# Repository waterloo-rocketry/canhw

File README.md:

## RocketCAN Hardware

This repository tracks the hardware development for the RocketCAN project. All schematics, board designs, and fabrication files are tracked in this repository. The corresponding software running on each board can be found in the `cansw_*` repositories. The CAN driver library used is tracked in the `canlib` repository.

All hardware files were developed in KiCAD.

### System Architecture

The RocketCAN project is an extension of the 2018 Flight Instrumentation project. The functions of the original Flight Instrumentation electronics are decoupled into several single-function modules connected by a Controller Area Network (CAN bus). The 2019 RocketCAN configuration consists of a radio board, an injector valve driver, a vent valve driver, a flight sensor suite, a system logger, and a GPS receiver. The modules freely share information over the CAN bus, allowing all modules to access resources such as the radio transceiver and sensor module. This minimizes the amount of component and functionality duplication, as well as power consumption (especially by the radio module). Power consumption is reduced further by allowing the radio board to control power to the rest of the system, forcing it into a low-power state while the rocket is idle. The resulting PCBs are also significantly smaller and easier to mount inside the rocket. Finally, RocketCAN’s configuration is easily extensible. A new subsystem simply needs to include a CAN communication module, after which it can communicate with all other boards on the bus. Potential extensions such as a flight computer, a state estimation module, or an air braking system would be able to use existing sensor data without implementing their own independent sensor suite.

At present, the radio board integrates with Waterloo Rocketry's Remote Launch Control System (RLCS), from which it receives instructions. It is also capable of broadcasting sensor data to RLCS.  The radio board communicates with the tower-side box of RLCS, which relays the data to the client-side box at mission control.

The CAN protocol was chosen for its high data rate, priority-based arbitration, and abundance of inexpensive hardware. The bus can safely be used by many boards at once without the risk of a low-priority message (eg. sensor data) preempting a high-priority message (eg. valve command). Microcontrollers with CAN modules, stand-alone CAN modules, and CAN transceivers are all widely available, making it cheap and simple to add CAN functionality to a subsystem.

Further descriptions and instructions for using each individual board are available in the README in the relevant board's directory.

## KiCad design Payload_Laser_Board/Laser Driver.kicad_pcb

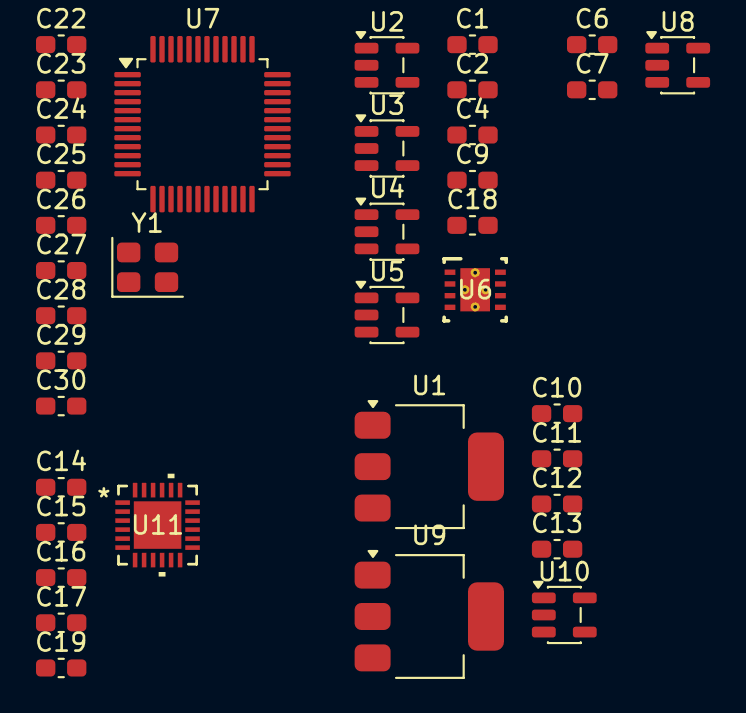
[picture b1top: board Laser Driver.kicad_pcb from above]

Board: 4 copper layers, 37 parts (0 on the bottom side), 25 nets, no tracks yet.

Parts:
C1: 0.47nF; C_0603_1608Metric_Pad1.08x0.95mm_HandSolder
C2: 2.2nF; C_0603_1608Metric_Pad1.08x0.95mm_HandSolder
C4, C9, C16, C17, C19, C25, C26: 0.1uF; C_0603_1608Metric_Pad1.08x0.95mm_HandSolder
C6: 35nF; C_0603_1608Metric_Pad1.08x0.95mm_HandSolder
C7: 160pF; C_0603_1608Metric_Pad1.08x0.95mm_HandSolder
C10, C11, C24, C27, C28, C29: 1uF; C_0603_1608Metric_Pad1.08x0.95mm_HandSolder
C12, C13, C22, C23: 2.2uF; C_0603_1608Metric_Pad1.08x0.95mm_HandSolder
C14, C15: 10uF; C_0603_1608Metric_Pad1.08x0.95mm_HandSolder
C18: 1nF; C_0603_1608Metric_Pad1.08x0.95mm_HandSolder
C30: 100nF; C_0603_1608Metric_Pad1.08x0.95mm_HandSolder
U1, U9: SPX2920M3-3.3_SOT223; SOT-223-3_TabPin2
U2, U3, U4, U5, U8: OPA364; SOT-23-5
U6: TPS73533QDRBRQ1; DRB0008B
U7: STM32H503CBTx; LQFP-48_7x7mm_P0.5mm
U10: INA160; SOT-23-5
U11: ADN8833ACPZ-R2; CP_24_7_ADI
Y1: ASE-8MHz; Oscillator_SMD_Abracon_ASE-4Pin_3.2x2.5mm

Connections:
+3.3VA: C4.1, C12.1, C24.2, U2.5 (V+), U3.5 (V+), U4.5 (V+), U5.5 (V+), U6.8 (IN), U7.9 (VDDA), U9.3 (VO)
+3.3VD: C13.1, C25.2, C26.2, C27.2, C28.2, C29.2, C30.2, U1.3 (VO), U7.1 (VBAT), U7.24 (VDD), U7.36 (VDD), U7.48 (VDD), U8.5 (V+), Y1.1 (EN), Y1.4 (Vdd)
+5V: C10.1, C11.1, C15.2, U1.1 (VI), U9.1 (VI), U10.3 (+), U11.15 (PVINS), U11.16 (PVINL)
/LASER_ENABLE_: C9.1, U6.5 (EN), U7.40 (PB4(NJTRST))
/MCU/CURRENT_SENSE: U7.18 (PB0), U10.1
/MCU/ITEC: U7.11 (PA1), U11.11 (TI_EC)
/MCU/OSC_IN: U7.5 (PH0), Y1.3 (OUT)
/MCU/VTEC: U7.12 (PA2), U11.9 (VTEC)
/MCU/VTEC_ENABLE: U7.13 (PA3), U11.2 (CONT)
/MCU/VTEC_ENB: U7.42 (PB6), U11.8 (EN_S/Y)
/SINE_SOURCE: C6.2, U7.15 (PA5)
GND: C4.2, C7.2, C9.2, C10.2, C11.2, C12.2, C13.2, C14.1, C15.1, C16.1, C17.1, C19.1, C22.1, C23.1, C24.1, C25.1, C26.1, C27.1, C28.1, C29.1, C30.1, U1.2 (GND), U2.2 (V-), U3.2 (V-), U4.2 (V-), U5.2 (V-), U6.4 (GND), U6.9 (PAD), U7.8 (VSSA), U7.23 (VSS), U7.35 (VSS), U7.47 (VSS), U8.2 (V-), U9.2 (GND), U10.2 (V-), U11.7 (AGND), U11.12 (PGNDS), U11.13 (PGNDS), U11.18 (PGNDL), U11.19 (PGNDL), U11.25 (EP), Y1.2 (GND)
unnamed: C22.2, U7.46 (VCAP)
unnamed: C23.2, U7.22 (VCAP)
unnamed: U2.1, U2.4 (-), U3.3 (+)
unnamed: U5.1, U5.4 (-)
unnamed: C2.1, C18.1, U6.1 (OUT)
unnamed: C17.2, U11.17 (LDR)
unnamed: C14.2, U11.10 (SFB)
unnamed: U3.4 (-), U4.1
unnamed: C18.2, U6.3 (FB)
unnamed: C7.1, U8.3 (+)
unnamed: U8.1, U8.4 (-)
unnamed: C16.2, U11.5 (VDD)
unnamed: C19.2, U11.6 (VREF)

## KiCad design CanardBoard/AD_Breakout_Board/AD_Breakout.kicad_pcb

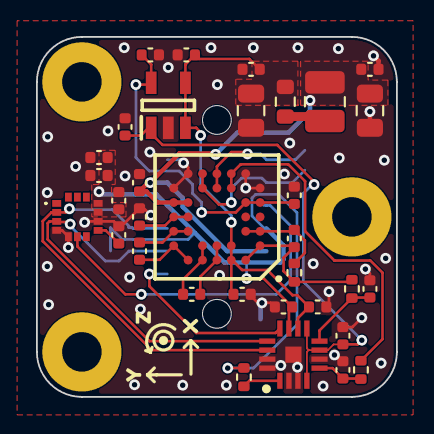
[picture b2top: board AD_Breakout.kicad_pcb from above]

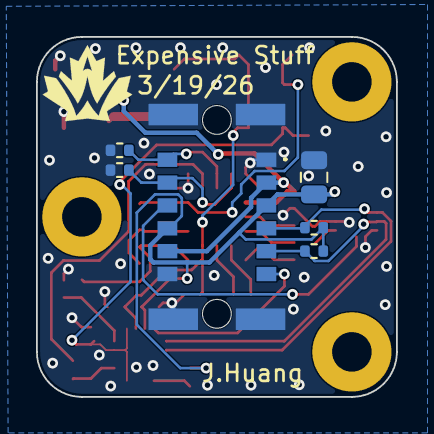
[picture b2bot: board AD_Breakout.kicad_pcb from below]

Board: 4 copper layers, 20.0 x 20.0 mm, 42 parts (6 on the bottom side), 25 nets.

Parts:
C1, C5, C7, C8, C11, C12, C13, C14, C15, C16, C19, C20, C22, C23, C24: 0.1uF; C_0402_1005Metric
C2, C3, C9: 22nF; C_0402_1005Metric
C4: 2.2nF; C_0402_1005Metric
C6: 6.8nF; C_0402_1005Metric
C10: 1uF; C_0402_1005Metric
C17, C18, C21: 10uF; C_0805_2012Metric
H1, H2, H3: M2; MountingHole_2.2mm_M2_Pad
J1: 1373827
L1: 2.2uH; L_1008_2520Metric
R1: 120k; R_0402_1005Metric
R2, R4: 3.3k; R_0402_1005Metric
R3, R5, R9: 10k; R_0402_1005Metric
R6, R7: 1k; R_0402_1005Metric
R8: 0.22R; R_0603_1608Metric
U1: ADXRS649BBGZ
U2: ADXL380
U3: ADS1219IRTER
U4: REF2041

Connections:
+2.048V_REF: C14.1, C24.1, U3.4 (AIN3), U3.7 (REFP), U3.9 (AIN0), U4.1 (VBIAS)
+3V3: C10.1, C11.1, C12.1, C16.1, C17.1, J1.A3, J1.B4, R6.1, R7.1, R9.1, U2.10 (VS), U2.11 (VDDIO), U3.11 (DVDD)
+4.096V_REF: C8.1, C23.1, U1.E1 (VRATIO_1), U1.E2 (VRATIO_2), U4.5 (VREF)
+5V: C1.1, C18.1, C19.1, J1.A2, J1.B5, L1.1, U1.E6 (VDD_1), U1.E7 (VDD_2)
+5VA: C5.1, C15.1, C20.1, C21.1, C22.1, R8.2, U1.A3 (AVCC_1), U1.B3 (AVCC_2), U3.10 (AVDD), U4.3 (EN), U4.4 (VIN)
/ADC/ADC_ALERT: J1.A6, U3.12 (~DRDY)
/ADC/ADI_SCL: J1.A4, R6.2, U2.2 (SCLK/SCL), U3.14 (SCL)
/ADC/ADI_SDA: J1.A5, R7.2, U2.3 (SDI/SDA), U3.13 (SDA)
/ADC/GYRO_OUT: C9.1, R4.2, U3.8 (AIN1)
/ADC/TEMP_OUT: C7.1, R2.2, U3.5 (AIN2)
/Accelerometer/ACCEL_INT: J1.B3, U2.6 (INT0)
/Gyroscope/TEMP: R2.1, U1.F3 (TEMP_1), U1.G3 (TEMP_2)
/ST1: J1.B2, R5.2, U1.F5 (ST1_1), U1.G5 (ST1_2)
/ST2: J1.B1, R3.2, U1.F4 (ST2_1), U1.G4 (ST2_2)
GND: C1.2, C4.2, C5.2, C7.2, C8.2, C9.2, C10.2, C11.2, C12.2, C13.2, C14.2, C15.2, C16.2, C17.2, C18.2, C19.2, C20.2, C21.2, C22.2, C23.2, C24.2, J1.A1, J1.B6, J1.MP1, J1.MP2, J1.MP3, J1.MP4, R3.1, R5.1, U1.F1 (AGND_1), U1.F7 (PGND_1), U1.G2 (AGND_2), U1.G6 (PGND_2), U2.4 (SDO/ASEL0), U2.5 (~CS/ASEL1), U2.9 (GND), U3.2 (DGND), U3.3 (AGND), U3.6 (REFN), U3.15 (A0), U3.16 (A1), U3.17 (EP), U4.2 (GND)
unnamed: L1.2, R8.1
unnamed: C2.1, U1.A5 (CP1_1), U1.B5 (CP1_2)
unnamed: C2.2, U1.A4 (CP2_1), U1.B4 (CP2_2)
unnamed: C3.1, U1.C6 (CP3_1), U1.C7 (CP3_2)
unnamed: C3.2, U1.A6 (CP4_1), U1.B7 (CP4_2)
unnamed: C4.1, U1.D6 (CP5_1), U1.D7 (CP5_2)
unnamed: C6.1, R1.2, R4.1, U1.A2 (RATEOUT_1), U1.B1 (RATEOUT_2)
unnamed: C6.2, R1.1, U1.C1 (SUMJ_1), U1.C2 (SUMJ_2)
unnamed: C13.1, U2.8 (V1P8)
unnamed: R9.2, U3.1 (~RESET)

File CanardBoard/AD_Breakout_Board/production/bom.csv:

Designator,Footprint,Quantity,Value,LCSC Part #
"C1, C11, C12, C13, C14, C15, C16, C19, C20, C22, C23, C24, C5, C7, C8",0402,15,0.1uF,
C10,0402,1,1uF,
"C17, C18, C21",0805,3,10uF,
"C2, C3, C9",0402,3,22nF,
C4,0402,1,2.2nF,
C6,0402,1,6.8nF,
J1,1373827,1,1373827,
L1,1008,1,2.2uH,LQM2HPN2R2MG0L
R1,0402,1,120k,
"R2, R4",0402,2,3.3k,
"R3, R5, R9",0402,3,10k,
"R6, R7",0402,2,1k,
R8,0603,1,0.22R,
U1,ADXRS649BBGZ,1,ADXRS649BBGZ,
U2,ADXL380,1,ADXL380,
U3,ADS1219IRTER,1,ADS1219IRTER,
U4,REF2041,1,REF2041,

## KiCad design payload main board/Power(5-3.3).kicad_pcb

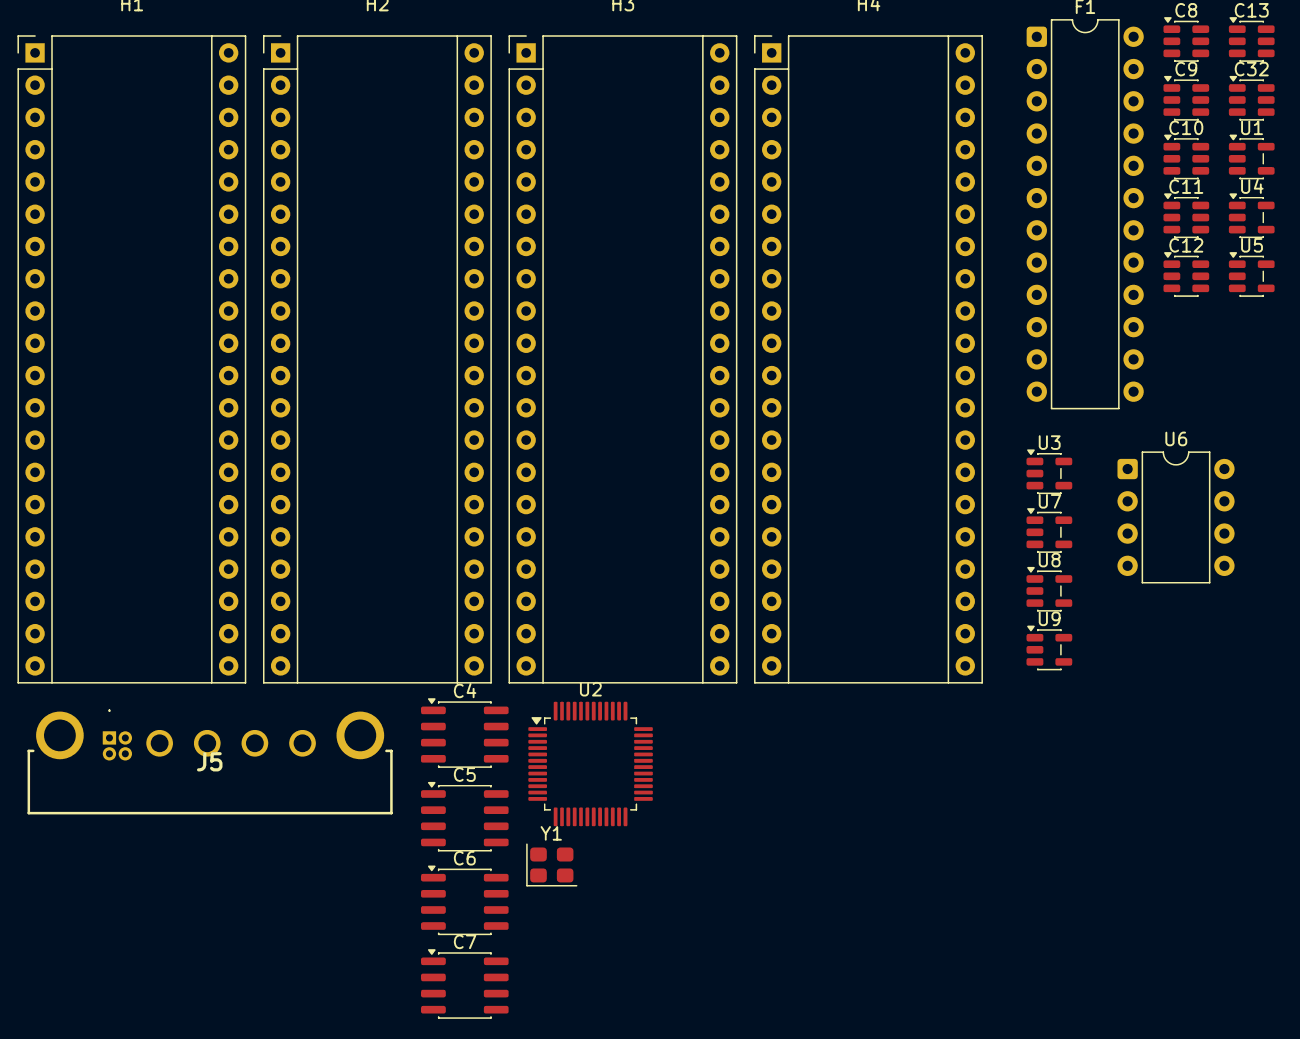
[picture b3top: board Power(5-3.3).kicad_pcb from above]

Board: 4 copper layers, 27 parts (0 on the bottom side), 19 nets, no tracks yet.

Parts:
C4: 100nF; SOIC-8_3.9x4.9mm_P1.27mm
C5: 1uF; SOIC-8_3.9x4.9mm_P1.27mm
C6, C7: 2.2uF; SOIC-8_3.9x4.9mm_P1.27mm
C8, C9, C12, C13: 1uF; SOT-23-6
C10, C11: 10nF; SOT-23-6
C32: 0.1uF; SOT-23-6
F1: 1A; DIP-24_W7.62mm
H1: MH1; Maple_Mini
H2: MH2; Maple_Mini
H3: MH3; Maple_Mini
H4: MH4; Maple_Mini
J5: G125-MH104M4-04AD000P; G125MH104M404AD000P
U1, U3, U7, U8, U9: INA180-A3; SOT-23-5
U2: STM32H503CBTx; LQFP-48_7x7mm_P0.5mm
U4, U5: SPX3819M5-L-3-3; SOT-23-5
U6: MCP2562-E-P; DIP-8_W7.62mm
Y1: ASE-xxxMHz; Oscillator_SMD_Abracon_ASE-4Pin_3.2x2.5mm

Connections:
+3.3VA: C4.2, C5.2, C13.1, U2.9 (VDDA), U5.5 (OUT)
+3.3VD: C12.1, C32.2, U1.5 (V+), U2.1 (VBAT), U2.24 (VDD), U2.36 (VDD), U2.48 (VDD), U3.3 (+), U3.5 (V+), U4.5 (OUT), U6.5 (Vio), U7.3 (+), U7.5 (V+), U8.3 (+), U8.5 (V+), U9.3 (+), U9.5 (V+), Y1.1 (EN), Y1.4 (Vdd)
+5V: C8.1, C9.1, U1.4 (-), U4.1 (IN), U4.3 (EN), U5.1 (IN), U5.3 (EN), U6.3 (VDD)
/CAN/CANH: J5.1 (CANH), U6.7 (CANH)
/CAN/CANL: J5.2 (CANL), U6.6 (CANL)
/CAN_RX: U2.21 (PB10), U6.4 (RXD)
/CAN_TX: U2.25 (PB12), U6.1 (TXD)
/CURRENT_SENSE_OUT: U1.1, U2.18 (PB0)
/J1_CURRENT_SENSE: U2.10 (PA0), U3.1
/J2_CURRENT_SENSE: U2.11 (PA1), U7.1
/J3_CURRENT_SENSE: U2.12 (PA2), U8.1
/J4_CURRENT_SENSE: U2.13 (PA3), U9.1
/OSC_IN: U2.5 (PH0), Y1.3 (OUT)
GND: C4.1, C5.1, C6.2, C7.2, C8.2, C9.2, C10.2, C11.2, C12.2, C13.2, C32.1, H1.1 (1_1), H2.1 (1_1), H3.1 (1_1), H4.1 (1_1), U1.2 (GND), U2.8 (VSSA), U2.23 (VSS), U2.35 (VSS), U2.47 (VSS), U3.2 (GND), U4.2 (GND), U5.2 (GND), U6.2 (VSS), U6.8 (STBY), U7.2 (GND), U8.2 (GND), U9.2 (GND), Y1.2 (GND)
unnamed: C6.1, U2.22 (VCAP)
unnamed: C7.1, U2.46 (VCAP)
unnamed: F1.1, U1.3 (+)
unnamed: C11.1, U4.4 (BP)
unnamed: C10.1, U5.4 (BP)

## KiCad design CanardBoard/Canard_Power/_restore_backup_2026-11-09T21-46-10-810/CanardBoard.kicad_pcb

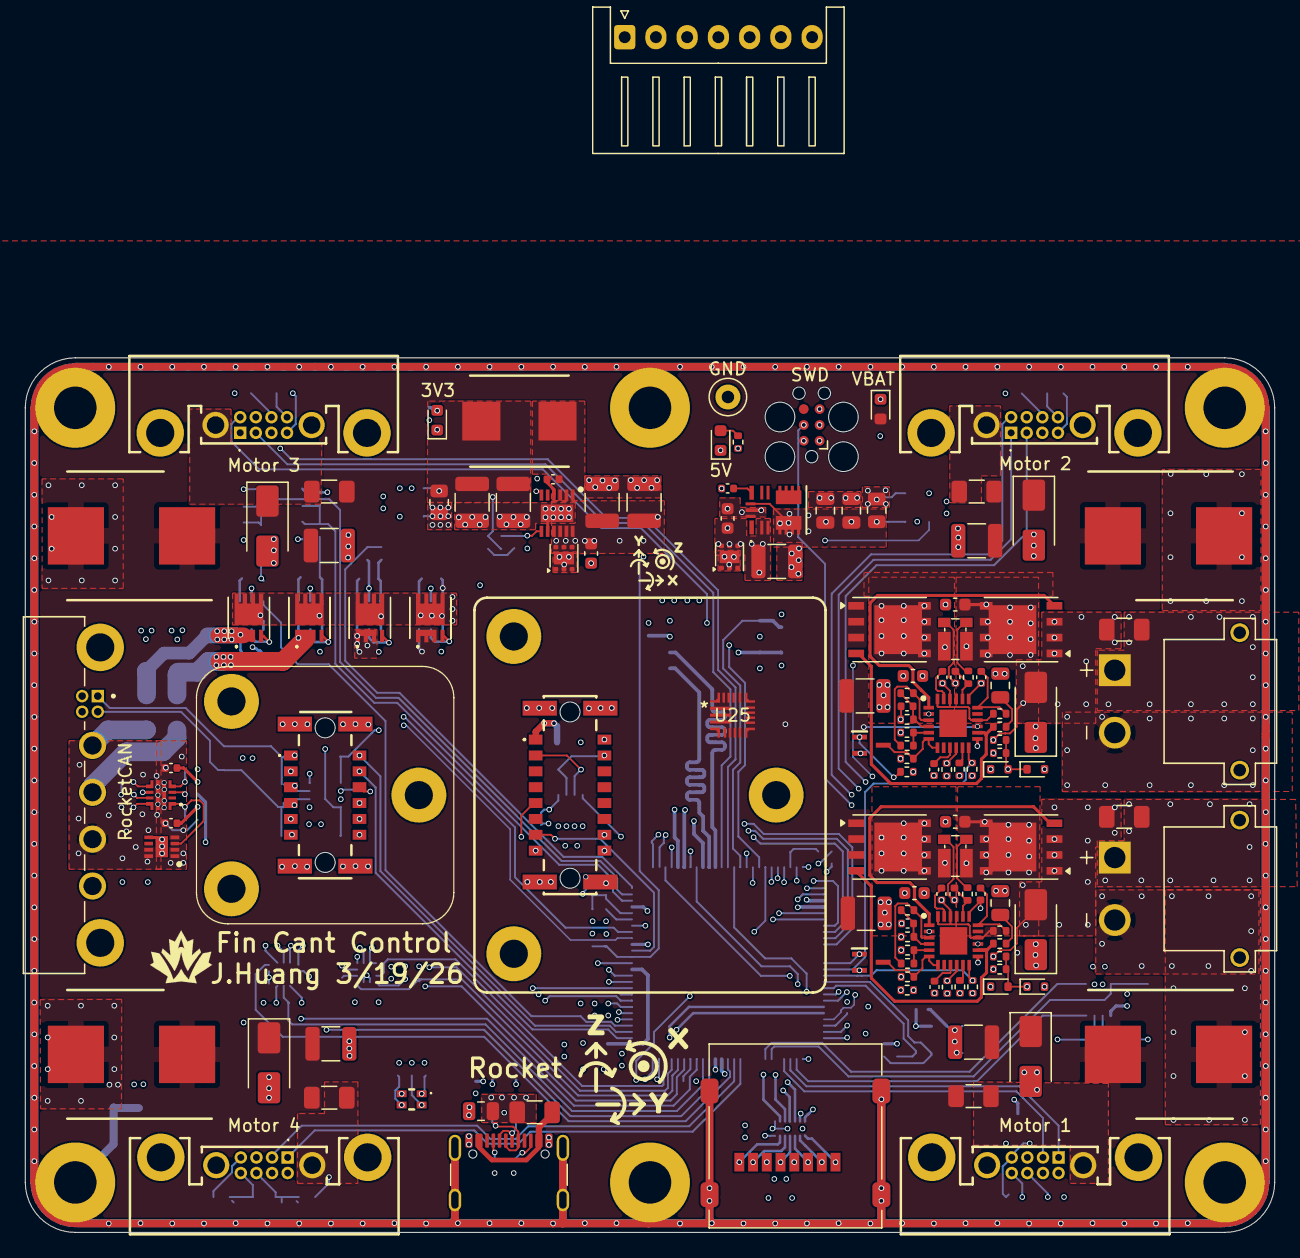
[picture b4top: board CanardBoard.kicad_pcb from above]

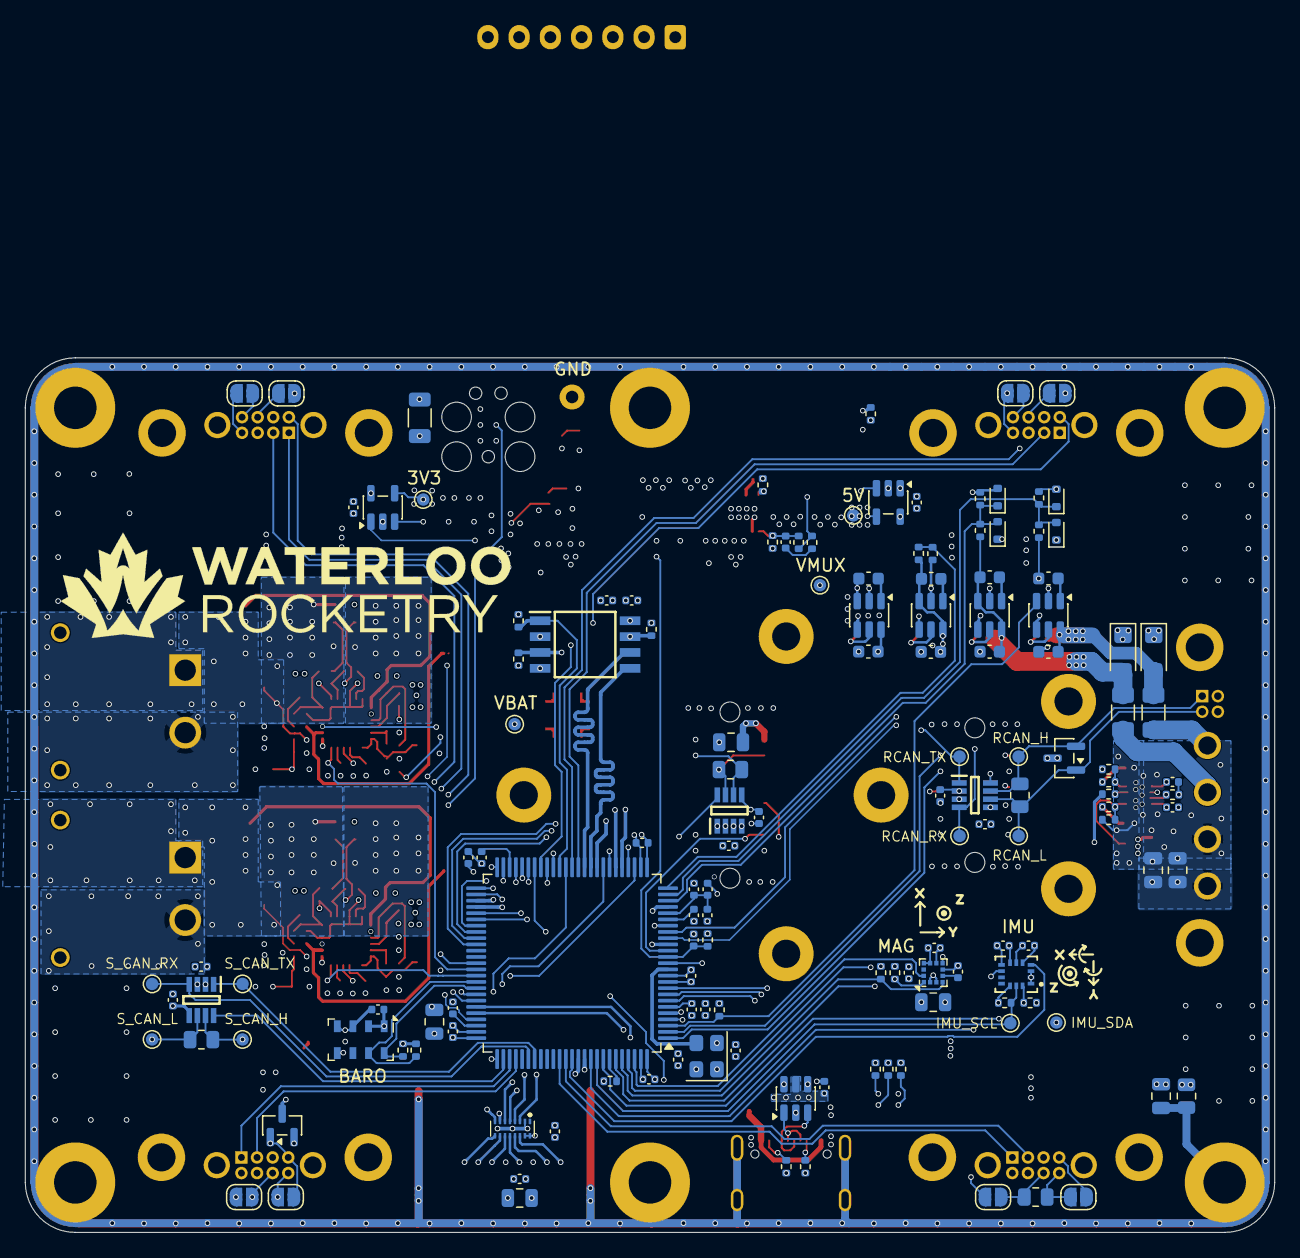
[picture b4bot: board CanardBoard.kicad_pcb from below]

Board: 6 copper layers, 100.0 x 70.0 mm, 276 parts (142 on the bottom side), 179 nets.

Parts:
C1, C6, C7, C8, C9, C10, C11, C14, C16, C18, C21, C22, C23, C24, C33, C34, C37, C40, C48, C50, C55, C57, C60, C61, C62, C66, C67, C73, C81, C82, C83, C84, C92, C93: 0.1uF; C_0402_1005Metric
C2, C4, C49: 2.2uF; C_0402_1005Metric
C3, C5, C13, C72, C91: 1uF; C_0402_1005Metric
C12, C17, C47, C56, C63, C65, C74, C76, C89: 22uF; C_0805_2012Metric
C15, C27, C28, C29, C30, C58, C59: 10nF; C_0402_1005Metric
C19, C20, C25, C26, C51, C52, C53, C54, C70, C71, C85, C86, C87, C88: 0.1uF; C_0603_1608Metric
C31, C32, C90: 0.1uF; C_0805_2012Metric
C35, C36, C38, C41, C43, C45, C68, C69, C79: 10uF; C_1210_3225Metric
C39, C42, C44, C46: 220uF; A786MW227M1HLAV011
C64: 220nF; C_0402_1005Metric
C75: 33pF; C_0402_1005Metric
C77, C78: 47uF; C_1210_3225Metric
D1: LED_RGBA; EAST1616RGBB2
D2, D3: SMAJ28CA; D_SMA
D4, D5, D6, D7, D13, D14, D15, D16: RB520S30T1G; D_SOD-523
D8, D9, D11, D12: SMAJ28A; D_SMA
D10, D17: ESDCAN01-2BLY; SOT-23
D18, D19: SMF15CA; D_SMF
D20, D21, D22: RED; LED_0603_1608Metric
F1, F2: 20A; Fuse_1206_3216Metric
F3, F4, F5, F6: 10A; Fuse_1206_3216Metric
F7, F8: 1.5A; Fuse_1206_3216Metric
F9: 5A; Fuse_1206_3216Metric
FB1: BLM15AG121SN1D; C_0402_1005Metric
H1, H2, H3, H4, H5, H6: M3; MountingHole_3.2mm_M3_Pad
J1: TagConnect_TC2030; Tag-Connect_TC2030-IDC-FP_2x03_P1.27mm_Vertical
J2: Micro_SD_Card; microSD_HC_Molex_47219-2001
J3, J4: XT30PW-M; AMASS_XT30PW-M
J5: Motor 2; G125MH10805M41AD1ADP
J6: Motor 1; G125MH10805M41AD1ADP
J7: Motor 4; G125MH10805M41AD1ADP
J8: Motor 3; G125MH10805M41AD1ADP
J9: USB_C_Receptacle_USB2.0_16P; USB_C_Receptacle_GCT_USB4105-xx-A_16P_TopMnt_Horizontal
J10: G125-MH104M4-04AD000P; connector_Harwin_G125-MH104M4-04AD000P
J11: Movella-1374028
J12: 1374027
J13: Balance Header; JST_XH_S7B-XH-A_1x07_P2.50mm_Horizontal
JP1, JP2, JP3, JP4, JP5, JP6, JP7, JP8: SolderJumper_2_Open; SolderJumper-2_P1.3mm_Open_RoundedPad1.0x1.5mm
L1: 4.7uH; SRP7050WA
Q1, Q2, Q3, Q4: SIR626DP-T1-RE3; PowerPAK_SO-8_Single
Q5, Q6: 2N7002W
Q7, Q8, Q9, Q10: 20N06D; Infineon-PG-TSDSON-8
R1, R2, R8, R14, R16, R33, R34, R37, R38, R41, R42, R47, R48, R49: 10k; R_0402_1005Metric
R3, R72, R73: 330R; R_0402_1005Metric
R4, R5, R27, R28: 100R; R_0402_1005Metric
R6, R7, R22, R24: 2.2k; R_0402_1005Metric
R9: 5.1k; R_1206_3216Metric
R13, R15, R17, R19, R21, R23, R35, R36, R39, R40, R50, R52, R54, R55, R56, R59, R61, R67: 100k; R_0402_1005Metric
R18, R20: 3.16k; R_0402_1005Metric
R25, R26, R66: 0R; R_0402_1005Metric
R29, R30: 1mR; R_Shunt_Vishay_WSKW0612
R31, R32: 10R; R_0402_1005Metric
R43, R44, R60, R65: 120R; R_0805_2012Metric
R45, R46: 5.1k; R_0402_1005Metric
R51, R53, R68: 19.1k; R_0402_1005Metric
R57: 34k; R_0402_1005Metric
R58: 681R; R_0402_1005Metric
R62: 43.2k; R_0402_1005Metric
R63, R64, R69, R74, R75: 1k; R_0402_1005Metric
R70, R71: 5m; R_0805_2012Metric
R76: 1M; R_0805_2012Metric
TP1: S_CAN_H; TestPoint_Pad_D1.0mm
TP2: S_CAN_L; TestPoint_Pad_D1.0mm
TP3: S_CAN_RX; TestPoint_Pad_D1.0mm
TP4: S_CAN_TX; TestPoint_Pad_D1.0mm
TP5: RCAN_H; TestPoint_Pad_D1.0mm
TP6: RCAN_L; TestPoint_Pad_D1.0mm
TP7: RCAN_RX; TestPoint_Pad_D1.0mm
TP8: RCAN_TX; TestPoint_Pad_D1.0mm
TP9: 3V3; TestPoint_Pad_D1.0mm
TP10: 5V; TestPoint_Pad_D1.0mm
TP11: VBAT; TestPoint_Pad_D1.0mm
TP12: VMUX; TestPoint_Pad_D1.0mm
TP13: GND; TestPoint_Loop_D2.50mm_Drill1.0mm
TP14: IMU_SCL; TestPoint_Pad_D1.0mm
TP15: IMU_SDA; TestPoint_Pad_D1.0mm
U1: STM32H733VGTx; LQFP-100_14x14mm_P0.5mm
U2: MS5611-01BA; LGA-8_3x5mm_P1.25mm
U3, U23: TVS3300DRV; WSON-6-1EP_2x2mm_P0.65mm_EP1x1.6mm
U4, U5: LM749x0
U6, U13, U16: TCAN3413DDFR
U7: USBLC6-2SC6; SOT-23-6
U8: MX25L25645GM2I-08G
U9, U10, U11, U12: LM74700; SOT-23-6
U14: TPS259472; TPS25947xx
U15: LSM303AGR; LGA-12_2x2mm_P0.5mm
U17: LMR51460
U18: TPSM33610S3QRDNRQ1; TPSM33606S3QRDNRQ1
U19, U20: INA180A3; SOT-23-5
U21: LSM6DSV32XTR
U22: EMIF06-MSD02N16; EMIF06MSD02N16
U24: TPS22975DSGR
U25: MP2759GQ-0000-P; QFN-19_MP2759_MNP
X1: ASE-4.000MHZ-L-C-T; Oscillator_SMD_Abracon_ASE-4Pin_3.2x2.5mm

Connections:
+3V3: C5.1, C6.1, C7.1, C8.1, C9.1, C10.1, C11.1, C12.1, C15.1, C16.1, C17.1, C18.1, C37.1, C40.1, C49.1, C50.1, C55.1, C57.1, C61.2, C62.2, C63.2, C66.1, C67.1, C81.2, C82.2, C83.1, C84.1, C92.1, C93.1, D1.4 (A), D4.1 (K), D6.1 (K), D13.1 (K), D15.1 (K), FB1.2, J1.1 (VCC), J2.4 (VDD), J12.A3 (3V3), J12.B4 (3V3), R1.1, R6.1, R7.1, R8.1, R33.2, R34.2, R47.1, R48.1, R49.1, R59.1, R63.2, R64.2, R70.1, R72.1, R74.1, R75.1, TP9.1 (1_1), U1.6 (VBAT), U1.11 (VDD), U1.27 (VDD), U1.50 (VDD), U1.75 (VDD), U1.100 (VDD), U2.1 (VDD), U2.2 (PS), U6.3 (VCC), U6.5 (VIO), U8.8 (VCC), U13.3 (VCC), U13.5 (VIO), U15.2 (CS_XL), U15.3 (CS_MAG), U15.9 (VDD), U15.10 (VDDIO), U16.3 (VCC), U16.5 (VIO), U19.4 (IN-), U19.5 (VS), U20.5 (VS), U21.5 (VDD_IO), U21.8 (VDD), U21.12 (CS), U22.15 (VCC), U22.16 (RDATA_VCC), X1.1 (EN), X1.4 (Vdd)
+5V: C60.1, C65.1, C91.1, J11.A1 (VIN), J12.A2 (5V), J12.B5 (5V), R61.1, R71.1, R73.1, TP10.1 (1_1), U14.5 (IN), U20.4 (IN-), U24.1 (VIN_1), U24.2 (VIN_2), U24.4 (VBIAS)
+5V_USB: C47.1, C48.1, C53.1, C87.1, F7.1, Q9.S, R54.1, U7.5 (VBUS), U11.3 (EN), U11.6 (ANODE)
+12V_RKT: C52.1, C86.1, D18.2 (A2), F9.2, Q8.S, R52.1, U10.3 (EN), U10.6 (ANODE)
+VBAT: C35.1, C36.1, C38.1, C39.1, C41.1, C42.1, C43.1, C44.1, C45.1, C46.1, C54.1, C88.1, D8.1 (A1), D9.1 (A1), D11.1 (A1), D12.1 (A1), D22.2 (A), F3.2, F4.2, F5.2, F6.2, Q3.S, Q4.S, Q10.S, TP11.1 (1_1), U4.15 (OUT), U5.15 (OUT), U12.3 (EN), U12.6 (ANODE)
+VCHG: C51.1, C85.1, D19.2 (A2), F8.2, Q7.S, R50.1, U9.6 (ANODE), U25.10 (CELL)
+VMUX: C68.2, C69.2, C70.2, C71.2, C79.2, Q7.D, Q8.D, Q9.D, Q10.D, TP12.1 (1_1), U3.4 (IN), U3.5 (IN), U3.6 (IN), U9.4 (CATHODE), U10.4 (CATHODE), U11.4 (CATHODE), U12.4 (CATHODE), U17.9 (EN), U17.10 (VIN_1), U17.11 (VIN_2), U17.12 (VIN_3), U18.2 (EN), U18.3 (VIN), U23.4 (IN), U23.5 (IN), U23.6 (IN)
/32G IMU/IMU_INT1: U1.88 (PD7), U21.4 (INT1)
/32G IMU/IMU_INT2: U1.91 (PB5), U21.9 (INT2)
/32G IMU/IMU_SCL: R75.2, TP14.1 (1_1), U1.92 (PB6), U21.13 (SCL)
/32G IMU/IMU_SDA: R74.2, TP15.1 (1_1), U1.93 (PB7), U21.14 (SDA)
/AD Breakout/ADC_INT: J12.A6 (ADC_ALERT), U1.42 (PE12)
/AD Breakout/ADI_SCL: J12.A4 (SCL), U1.46 (PB10)
/AD Breakout/ADI_SDA: J12.A5 (SDA), U1.47 (PB11)
/AD Breakout/ADXL_INT: J12.B3 (ACCEL_INT), U1.45 (PE15)
/AD Breakout/ADXRS_ST1: J12.B2 (ST1), U1.1 (PE2)
/AD Breakout/ADXRS_ST2: J12.B1 (ST2), U1.2 (PE3)
/Barometer/BAR_SCL: R6.2, U1.67 (PA8), U2.8 (SCLK)
/Barometer/BAR_SDA: R7.2, U1.66 (PC9), U2.7 (SDI/SDA)
/Flash/FLASH_CLK: U1.36 (PB2), U8.6 (SCLK)
/Flash/FLASH_CS: R47.2, U1.40 (PE10), U8.1 (CS#)
/Flash/FLASH_IO0: U1.35 (PB1), U8.5 (SI/SIO0)
/Flash/FLASH_IO1: U1.34 (PB0), U8.2 (SO/SIO1)
/Flash/FLASH_IO2: R48.2, U1.31 (PA7), U8.3 (WP#/SIO2)
/Flash/FLASH_IO3: R49.2, U1.30 (PA6), U8.7 (RESET#/SIO3)
/Magnetometer/INT1_MAG_ACCEL: U1.98 (PE1), U15.12 (INT_1_XL)
/Magnetometer/INT_MAG: U1.97 (PE0), U15.7 (INT_MAG/DRDY)
/Magnetometer/MAG_SCL: R64.1, U1.95 (PB8), U15.1 (SCL/SPC)
/Magnetometer/MAG_SDA: R63.1, U1.96 (PB9), U15.4 (SDA/SDI/SDO)
/Movella/MCAN_H: J11.A2 (CAN_H), R65.2, U16.7 (CANH)
/Movella/MCAN_L: J11.B2 (CAN_L), R65.1, U16.6 (CANL)
/Power Input/BAT1_IN: C19.1, D2.2 (A2), F1.1, Q1.S, R13.1, R39.1, U4.2 (A)
/Power Input/BAT2_IN: C20.1, D3.2 (A2), F2.1, Q2.S, R15.1, R40.1, U5.2 (A)
/Power Input/BAT_FLT1: R33.1, U1.64 (PC7), U4.12 (~FLT)
/Power Input/BAT_FLT2: R34.1, U1.65 (PC8), U5.12 (~FLT)
/Power Input/ISENS_BAT1: R37.1, U1.29 (PA5), U4.10 (IMON)
/Power Input/ISENS_BAT2: R38.1, U1.28 (PA4), U5.10 (IMON)
/Power Input/PWR_EN: Q5.1 (G), Q6.1 (G), R41.2, R42.2, U1.63 (PC6)
/Power Input/VSENS_BAT1: D4.2 (A), D5.1 (K), R13.2, R14.1, U1.32 (PC4)
/Power Input/VSENS_BAT2: D6.2 (A), D7.1 (K), R15.2, R16.1, U1.33 (PC5)
/Power Muxing/CHG_MUX_EN: R8.2, U1.3 (PE4), U9.3 (EN)
/Power Muxing/VSENS_CHG: D13.2 (A), D14.1 (K), R50.2, R51.2, U1.24 (PA2)
/Power Muxing/VSENS_RKT: D15.2 (A), D16.1 (K), R52.2, R53.2, U1.23 (PA1)
/Power Muxing/VSENS_USB: R54.2, R55.2, U1.25 (PA3)
/Power Rails/ISENS_3V3: U1.17 (PC2_C), U19.1 (VO)
/Power Rails/ISENS_5V: U1.18 (PC3_C), U20.1 (VO)
/Processor/EN_EXT_5V: R61.2, R62.1, U1.4 (PE5), U14.1 (EN/UVLO), U24.3 (ON)
/Processor/LED_B: R5.2, U1.9 (PC15)
/Processor/LED_G: R4.2, U1.8 (PC14)
/Processor/LED_R: R3.2, U1.7 (PC13)
/Processor/NRST: C1.1, J1.3 (~RESET), R1.2, U1.14 (NRST)
/Processor/PG_EXT_5V: R59.2, U1.5 (PE6), U14.3 (PG)
/Processor/PWM1: J6.5, U1.39 (PE9)
/Processor/PWM2: J5.5, U1.41 (PE11)
/Processor/PWM3: J8.5, U1.43 (PE13)
/Processor/PWM4: J7.5, U1.44 (PE14)
/Processor/RCAN_RX: TP7.1 (1_1), U1.59 (PD12), U13.4 (RXD)
/Processor/RCAN_STB: U1.58 (PD11), U13.8 (STB)
/Processor/RCAN_TX: TP8.1 (1_1), U1.60 (PD13), U13.1 (TXD)
/Processor/RCC_osc_In: U1.12 (PH0), X1.3 (OUT)
/Processor/SD_CLK: U1.16 (PC1), U22.5 (CLK_IN)
/Processor/SD_CMD: U1.22 (PA0), U22.6 (CMD_IN)
/Processor/SD_D0: U1.53 (PB14), U22.4 (DAT0_IN)
/Processor/SD_D1: U1.54 (PB15), U22.3 (DAT1_IN)
/Processor/SD_D2: U1.89 (PB3(JTDO), U22.8 (DAT2_IN)
/Processor/SD_D3: U1.90 (PB4(NJTRST)), U22.7 (DAT3_IN)
/Processor/SERVO1_RX: J6.2, U1.79 (PC11)
/Processor/SERVO1_TX: J6.1, U1.78 (PC10)
/Processor/SERVO2_RX: J5.2, U1.69 (PA10)
/Processor/SERVO2_TX: J5.1, U1.68 (PA9)
/Processor/SERVO3_RX: J8.2, U1.37 (PE7)
/Processor/SERVO3_TX: J8.1, U1.38 (PE8)
/Processor/SERVO4_RX: J7.2, U1.87 (PD6)
/Processor/SERVO4_TX: J7.1, U1.86 (PD5)
/Processor/S_CAN_RX: TP3.1 (1_1), U1.81 (PD0), U6.4 (RXD)
/Processor/S_CAN_STB: U1.77 (PA15(JTDI)), U6.8 (STB)
/Processor/S_CAN_TX: TP4.1 (1_1), U1.82 (PD1), U6.1 (TXD)
/Processor/USB_D+: U1.71 (PA12), U7.4 (I/O2)
/Processor/USB_D-: U1.70 (PA11), U7.6 (I/O1)
/Processor/VCAP1: C2.2, U1.48 (VCAP)
/Processor/VCAP2: C4.2, U1.73 (VCAP)
/Processor/VDDA: C13.1, C14.1, FB1.1, U1.21 (VDDA)
/RocketCAN/RCAN_H: D17.2 (K), J10.1 (CANH), R60.2, TP5.1 (1_1), U13.7 (CANH)
/RocketCAN/RCAN_L: D17.1 (K), J10.2 (CANL), R60.1, TP6.1 (1_1), U13.6 (CANL)
/RocketCAN/RKT_5V_OUT: C56.1, C89.1, J10.C (+5V), R56.1, U14.6 (OUT), U24.7 (VOUT_1), U24.8 (VOUT_2)
/SD_Card/CLK_CARD: J2.5 (CLK), U22.12 (CLK_EX)
/SD_Card/CMD_CARD: J2.3 (CMD), U22.11 (CMD_EX)
/SD_Card/DAT0_CARD: J2.7 (DAT0), U22.13 (DAT0_EX)
/SD_Card/DAT1_CARD: J2.8 (DAT1), U22.14 (DAT1_EX)
/SD_Card/DAT2_CARD: J2.1 (DAT2), U22.9 (DAT2_EX)
/SD_Card/DAT3_CARD: J2.2 (DAT3/CD), U22.10 (DAT3_EX)
/Servos/CANH_4: J7.7, JP3.2 (B), R44.1
/Servos/CANH_12: J5.3, J6.7, JP1.2 (B), JP7.1 (A)
/Servos/CANH_23: J5.7, J8.3, JP5.1 (A), JP7.2 (B)
/Servos/CANH_34: J7.3, J8.7, JP3.1 (A), JP5.2 (B)
/Servos/CANL_4: J7.8, JP4.2 (B), R44.2
/Servos/CANL_12: J5.4, J6.8, JP2.2 (B), JP8.1 (A)
/Servos/CANL_23: J5.8, J8.4, JP6.1 (A), JP8.2 (B)
/Servos/CANL_34: J7.4, J8.8, JP4.1 (A), JP6.2 (B)
/Servos/S_CAN_H: D10.2 (K), J6.3, JP1.1 (A), R43.2, TP1.1 (1_1), U6.7 (CANH)
/Servos/S_CAN_L: D10.1 (K), J6.4, JP2.1 (A), R43.1, TP2.1 (1_1), U6.6 (CANL)
GND: C1.2, C2.1, C3.2, C4.1, C5.2, C6.2, C7.2, C8.2, C9.2, C10.2, C11.2, C12.2, C13.2, C14.2, C15.2, C16.2, C17.2, C18.2, C19.2, C20.2, C21.2, C22.2, C25.2, C26.2, C31.2, C32.2, C33.2, C34.2, C35.2, C36.2, C37.2, C38.2, C39.2, C40.2, C41.2, C42.2, C43.2, C44.2, C45.2, C46.2, C47.2, C48.2, C49.2, C50.2, C55.2, C56.2, C57.2, C58.2, C59.2, C60.2, C61.1, C62.1, C63.1, C64.1, C65.2, C66.2, C67.2, C68.1, C69.1, C70.1, C71.1, C72.1, C74.1, C76.1, C77.1, C78.1, C79.1, C81.1, C82.1, C83.2, C84.2, C85.2, C86.2, C87.2, C88.2, C89.2, C90.2, C91.2, C92.2, C93.2, D2.1 (A1), D3.1 (A1), D5.2 (A), D7.2 (A), D8.2 (A2), D9.2 (A2), D10.3 (A), D11.2 (A2), D12.2 (A2), D14.2 (A), D16.2 (A), D17.3 (A), D18.1 (A1), D19.1 (A1), D20.1 (K), D21.1 (K), J1.5 (GND), J2.6 (VSS), J3.N, J4.N, J5.6, J5.10 (A2), J6.6, J6.10 (A2), J7.6, J7.10 (A2), J8.6, J8.10 (A2), J9.A1 (GND), J9.A12 (GND), J9.B1 (GND), J9.B12 (GND), J10.D (GND), J11.B1 (GND), J11.B7 (GND), J11.MP1, J11.MP2, J11.MP3, J11.MP4, J12.A1 (GND), J12.B6 (GND), J12.MP1, J12.MP2, J12.MP3, J12.MP4, Q5.2 (S), Q6.2 (S), R2.2, R9.2, R14.2, R16.2, R18.2, R20.2, R22.2, R24.2, R35.2, R36.2, R37.2, R38.2, R41.1, R42.1, R45.2, R46.2, R51.1, R53.1, R55.1, R57.2, R58.2, R62.2, R66.1, R68.1, R76.2, TP13.1 (1_1), U1.10 (VSS), U1.19 (VSSA), U1.26 (VSS), U1.49 (VSS), U1.74 (VSS), U1.99 (VSS), U2.3 (GND), U2.4 (CSB), U2.5 (CSB), U3.1 (GND), U3.2 (GND), U3.3 (GND), U3.7 (GND), U4.13 (GND), U5.13 (GND), U6.2 (GND), U7.2 (GND), U8.4 (GND), U9.2 (GND), U10.2 (GND), U11.2 (GND), U12.2 (GND), U13.2 (GND), U14.8 (GND), U15.6 (GND), U15.8 (GND), U16.2 (GND), U17.8 (AGND), U17.13 (PGND/DAP), U18.10 (GND), U18.11 (MODE/SYNCH), U19.2 (GND), U20.2 (GND), U21.1 (SDO/SA0), U21.2 (SDX/AH1/QVAR1), U21.3 (SCX/AH2/QVAR2), U21.6 (GND), U21.7 (GND), U22.2 (RDAT3_GND), U22.17 (EP_(GND)), U23.1 (GND), U23.2 (GND), U23.3 (GND), U23.7 (GND), U24.5 (GND), U24.9 (EP), U25.6 (PGND), U25.7 (PGND), U25.16 (AGND), X1.2 (GND)
unnamed: C31.1, R31.2
unnamed: C32.1, R32.2
unnamed: C75.2, R69.1
unnamed: D1.3 (BK), R5.1
unnamed: D1.2 (GK), R4.1
unnamed: D1.1 (RK), R3.1
unnamed: D20.2 (A), R72.2
unnamed: D21.2 (A), R73.2
unnamed: D22.1 (K), R9.1
unnamed: F1.2, J3.P
unnamed: F2.2, J4.P
unnamed: F7.2, J9.A4 (VBUS), J9.A9 (VBUS), J9.B4 (VBUS), J9.B9 (VBUS)
unnamed: J1.4 (SWCLK), U1.76 (PA14(JTCK)
unnamed: J1.2 (SWDIO), U1.72 (PA13(JTMS)
unnamed: F3.1, J5.9 (A1)
unnamed: F4.1, J6.9 (A1)
unnamed: F5.1, J7.9 (A1)
unnamed: F6.1, J8.9 (A1)
unnamed: J9.A5 (CC1), R46.1
unnamed: J9.B5 (CC2), R45.1
unnamed: J9.A6 (D+), J9.B6 (D+), U7.3 (I/O2)
unnamed: J9.A7 (D-), J9.B7 (D-), U7.1 (I/O1)
unnamed: F9.1, J10.B (+12V)
unnamed: F8.1, J10.A (+CHG)
unnamed: Q3.D, R29.1
unnamed: Q4.D, R30.1
unnamed: Q5.3 (D), R39.2, U4.6 (EN), U4.7 (~SLEEP)
unnamed: Q6.3 (D), R40.2, U5.6 (EN), U5.7 (~SLEEP)
unnamed: R27.1, R29.3
unnamed: R28.1, R30.3
unnamed: R2.1, U1.94 (BOOT0)
unnamed: C3.1, U1.20 (VREF+)
unnamed: C23.1, C25.1, Q1.D, R25.1, R29.4, U4.16 (SLEEP_OV), U4.22 (VS), U4.24 (C)
unnamed: C23.2, U4.23 (CAP)
unnamed: C27.1, R27.2, U4.20 (CS+)
unnamed: C27.2, C28.2, R29.2, U4.19 (CS-)
unnamed: Q1.G, U4.1 (DGATE)
unnamed: Q3.G, R31.1, U4.14 (HGATE)
unnamed: R35.1, U4.11 (ILIM)
unnamed: C28.1, R25.2, U4.18 (ISCP)
unnamed: R21.2, R22.1, U4.5 (OV)
unnamed: R17.1, R21.1, U4.3 (SW)
unnamed: C33.1, U4.9 (TMR)
unnamed: C21.1, R17.2, R18.1, U4.4 (UVLO)
unnamed: C24.1, C26.1, Q2.D, R26.1, R30.4, U5.16 (SLEEP_OV), U5.22 (VS), U5.24 (C)
unnamed: C24.2, U5.23 (CAP)
unnamed: C29.1, R28.2, U5.20 (CS+)
unnamed: C29.2, C30.2, R30.2, U5.19 (CS-)
unnamed: Q2.G, U5.1 (DGATE)
unnamed: Q4.G, R32.1, U5.14 (HGATE)
unnamed: R36.1, U5.11 (ILIM)
unnamed: C30.1, R26.2, U5.18 (ISCP)
unnamed: R23.2, R24.1, U5.5 (OV)
unnamed: R19.1, R23.1, U5.3 (SW)
unnamed: C34.1, U5.9 (TMR)
unnamed: C22.1, R19.2, R20.1, U5.4 (UVLO)
unnamed: Q7.G, U9.5 (GATE)
unnamed: C51.2, U9.1 (VCAP)
unnamed: Q8.G, U10.5 (GATE)
unnamed: C52.2, U10.1 (VCAP)
unnamed: Q9.G, U11.5 (GATE)
unnamed: C53.2, U11.1 (VCAP)
unnamed: Q10.G, U12.5 (GATE)
unnamed: C54.2, U12.1 (VCAP)
unnamed: C58.1, U14.7 (DVDT)
unnamed: R58.1, U14.9 (ILM)
unnamed: C59.1, U14.10 (ITIMER)
unnamed: R56.2, R57.1, U14.4 (PGTH)
unnamed: C64.2, U15.5 (C1)
unnamed: C73.2, U17.4 (BOOT)
unnamed: C75.1, R67.1, R68.2, U17.7 (FB)
unnamed: R66.2, U17.6 (RT)
unnamed: C73.1, L1.1, U17.1 (SW_1), U17.2 (SW_2), U17.3 (SW_3)
unnamed: C74.2, C76.2, R70.2, U18.4 (VOUT), U18.9 (FB), U19.3 (IN+)
unnamed: C72.2, U18.8 (VCC)
unnamed: C77.2, C78.2, L1.2, R67.2, R69.2, R71.2, U20.3 (IN+)
SHIELD: C90.1, H1.1 (1_1), H2.1 (1_1), H3.1 (1_1), H4.1 (1_1), H5.1 (1_1), H6.1 (1_1), J2.9 (SHIELD), J9.S1 (SHIELD), R76.1

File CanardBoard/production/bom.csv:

Designator,Footprint,Quantity,Value,LCSC Part #
"C1, C10, C11, C14, C16, C18, C21, C22, C23, C24, C33, C34, C37, C40, C48, C50, C55, C57, C6, C60, C61, C62, C66, C67, C7, C73, C8, C81, C82, C83, C84, C9, C92, C93",0402,34,0.1uF,C85858
"C12, C17, C47, C56, C63, C65, C74, C76, C89",0805,9,22uF,C86816
"C13, C3, C5, C72, C91",0402,5,1uF,C77007
"C15, C27, C28, C29, C30, C58, C59",0402,7,10nF,C91601
"C19, C20, C25, C26, C51, C52, C53, C54, C70, C71, C85, C86, C87, C88",0603,14,0.1uF,C3011652
"C2, C4, C49",0402,3,2.2uF,C77002
"C31, C32, C90",0805,3,0.1uF,C882587
"C35, C36, C38, C41, C43, C45, C68, C69, C79",1210,9,10uF,C77102
"C39, C42, C44, C46",A786MW227M1HLAV011,4,220uF,A786MW227M1HLAV011
C64,0402,1,220nF,C126524
C75,0402,1,33pF,C126506
"C77, C78",1210,2,47uF,C77101
D1,EAST1616RGBB2,1,LED_RGBA,C6606484
"D10, D17",SOT-23,2,ESDCAN01-2BLY,C1976606
"D11, D12, D8, D9",D_SMA,4,SMAJ28A,C148227
"D13, D14, D15, D16, D4, D5, D6, D7",D_SOD-523,8,RB520S30T1G,C154821
"D18, D19",D_SMF,2,SMF15CA,C1851361
"D2, D3",D_SMA,2,SMAJ28CA,C148228
"D20, D21, D22",0603,3,RED,C2986060
"F1, F2",1206,2,20A,C2838910
"F3, F4, F5, F6",1206,4,10A,C41367232
"F7, F8",1206,2,1.5A,C883133
F9,1206,1,5A,C41367229
FB1,0402,1,BLM15AG121SN1D,C85812
J10,connector_Harwin_G125-MH104M4-04AD000P,1,G125-MH104M4-04AD000P,
J11,Movella-1374028,1,Movella-1374028,
J12,1374027,1,1374027,
J2,microSD_HC_Molex_47219-2001,1,Micro_SD_Card,C164170
"J3, J4",AMASS_XT30PW-M,2,XT30PW-M,
J5,G125MH10805M41AD1ADP,1,Motor 2,
J6,G125MH10805M41AD1ADP,1,Motor 1,
J7,G125MH10805M41AD1ADP,1,Motor 4,
J8,G125MH10805M41AD1ADP,1,Motor 3,
J9,USB_C_Receptacle_GCT_USB4105-xx-A_16P_TopMnt_Horizontal,1,USB_C_Receptacle_USB2.0_16P,C165948
L1,SRP7050WA,1,4.7uH,C19947706
"Q1, Q2, Q3, Q4",PowerPAK_SO-8_Single,4,SIR626DP-T1-RE3,
"Q10, Q7, Q8, Q9",Infineon-PG-TSDSON-8,4,20N06D,C7543835
"Q5, Q6",2N7002W,2,2N7002W,C232391
"R1, R14, R16, R2, R33, R34, R37, R38, R41, R42, R47, R48, R49, R8",0402,14,10k,C144807
"R13, R15, R17, R19, R21, R23, R35, R36, R39, R40, R50, R52, R54, R55, R56, R59, R61, R67",0402,18,100k,C144809
"R18, R20",0402,2,3.16k,C227034
"R22, R24, R6, R7",0402,4,2.2k,C144773
"R25, R26",0402,2,0R,C226739
"R27, R28, R4, R5",0402,4,100R,C144808
"R29, R30",R_Shunt_Vishay_WSKW0612,2,1mR,C1517439
"R3, R72, R73",0402,3,330R,C226996
"R31, R32",0402,2,10R,C144805
"R43, R44, R65",0805,3,120R,C727984
"R45, R46",0402,2,5.1k,C144745
"R51, R53, R68",0402,3,19.1k,C226835
R57,0402,1,34k,C227006
R58,0402,1,681R,C416567
R62,0402,1,43.2k,C278596
"R63, R64, R69, R74, R75",0402,5,1k,C144789
"R70, R71",0805,2,5m,C728267
R76,0805,1,1M,C228604
R9,1206,1,5.1k,C229719
U1,LQFP-100_14x14mm_P0.5mm,1,STM32H733VGTx,
"U10, U11, U12, U9",SOT-23-6,4,LM74700,
"U13, U16, U6",TCAN3413DDFR,3,TCAN3413DDFR,
U14,TPS25947xx,1,TPS259472,C3662789
U15,LGA-12_2x2mm_P0.5mm,1,LSM303AGR,
U17,LMR51460,1,LMR51460,C41802645
U18,TPSM33606S3QRDNRQ1,1,TPSM33610S3QRDNRQ1,
"U19, U20",SOT-23-5,2,INA180A3,C122882
U2,LGA-8_3x5mm_P1.25mm,1,MS5611-01BA,
U21,LSM6DSV32XTR,1,LSM6DSV32XTR,
U22,EMIF06MSD02N16,1,EMIF06-MSD02N16,C5267594
"U23, U3",WSON-6-1EP_2x2mm_P0.65mm_EP1x1.6mm,2,TVS3300DRV,C2863624
"U4, U5",LM749x0,2,LM749x0,
U7,SOT-23-6,1,USBLC6-2SC6,C7519
U8,MX25L25645GM2I-08G,1,MX25L25645GM2I-08G,
X1,Oscillator_SMD_Abracon_ASE-4Pin_3.2x2.5mm,1,ASE-4.000MHZ-L-C-T,C437121

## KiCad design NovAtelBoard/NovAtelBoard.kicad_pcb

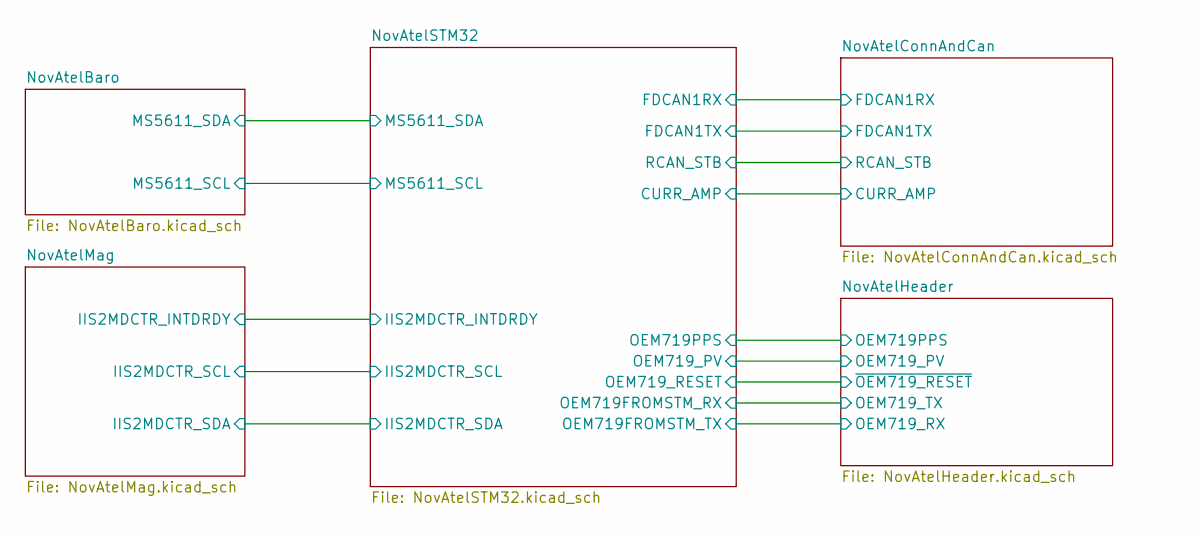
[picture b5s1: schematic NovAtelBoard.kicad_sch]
